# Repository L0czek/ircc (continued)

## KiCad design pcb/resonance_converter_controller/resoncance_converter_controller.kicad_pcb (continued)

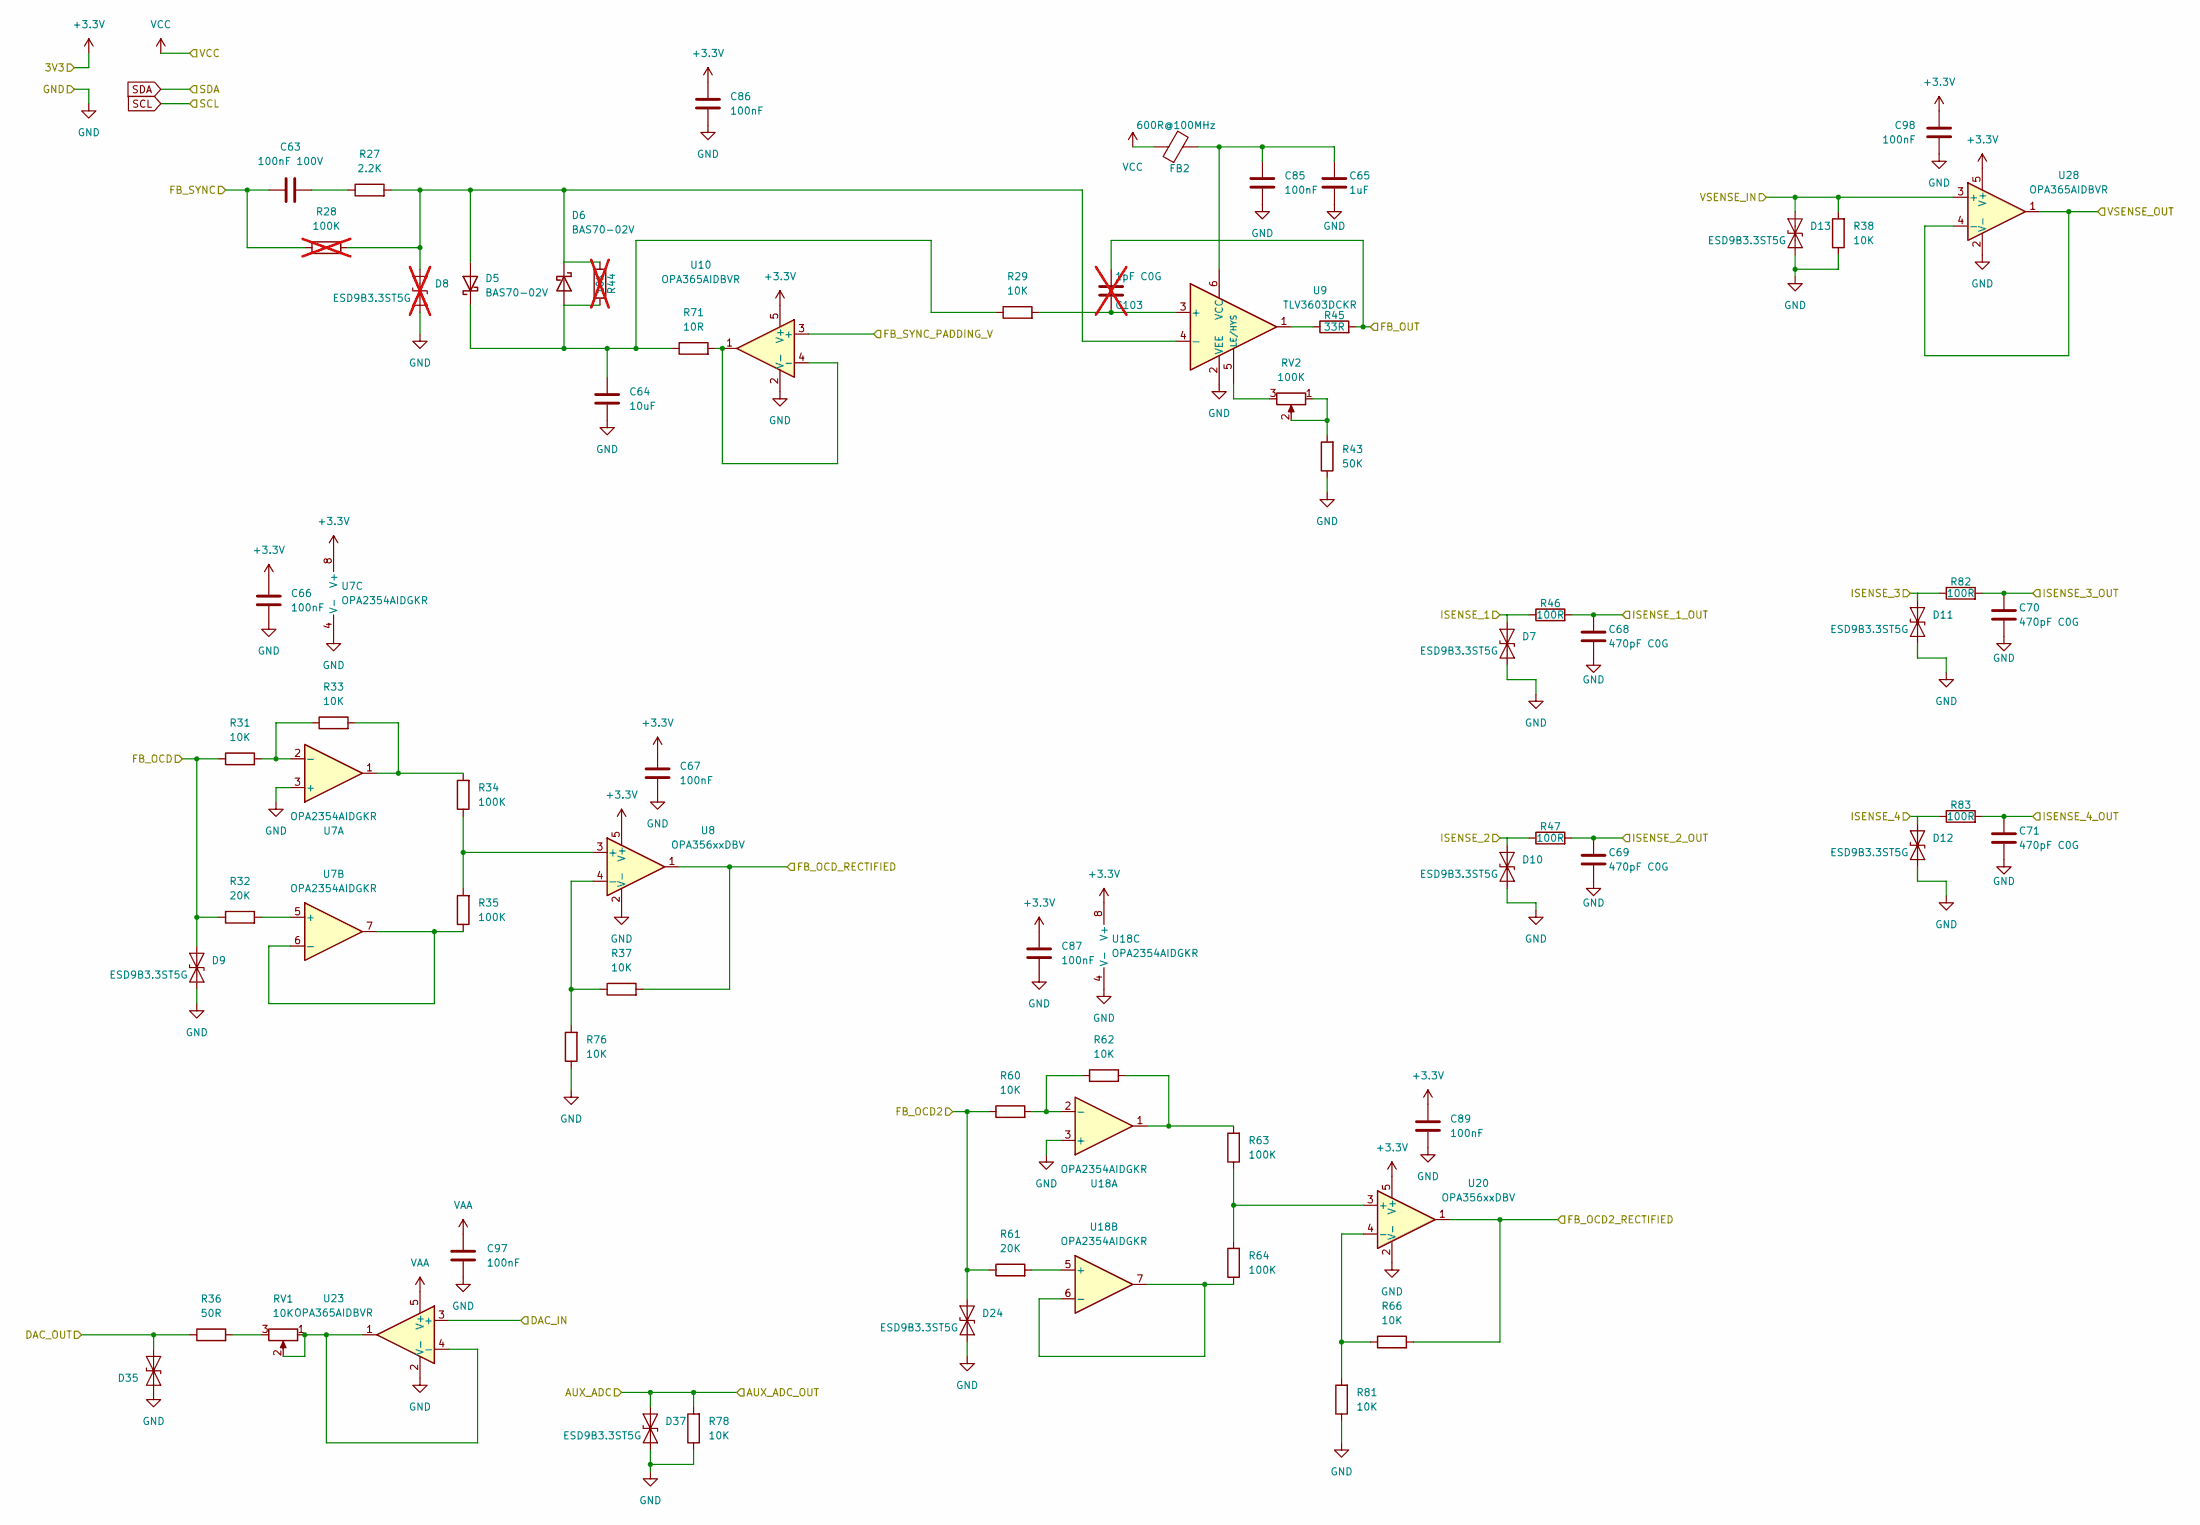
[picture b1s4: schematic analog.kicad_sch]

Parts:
C63: 100nF 100V; C_1206_3216Metric
C64: 10uF; C_1206_3216Metric
C65: 1uF; C_0402_1005Metric
C66, C67, C85, C86, C87, C89, C97, C98: 100nF; C_0402_1005Metric
C68, C69, C70, C71: 470pF C0G; C_0402_1005Metric
C103: 1pF C0G; C_0402_1005Metric; not fitted
D5, D6: BAS70-02V; D_SOD-523; MPN BAS7002VH6327XTSA1; LCSC C3312927
D7, D9, D10, D11, D12, D13, D24, D35, D37: ESD9B3.3ST5G; D_SOD-923
D8: ESD9B3.3ST5G; D_SOD-923; not fitted
FB2: 600R@100MHz; L_0603_1608Metric; MPN BLM18KG601SN1D; LCSC C85833
R27: 2.2K; R_2512_6332Metric
R28: 100K; R_1206_3216Metric; not fitted
R29, R31, R33, R37, R38, R60, R62, R66, R76, R78, R81: 10K; R_0402_1005Metric
R32, R61: 20K; R_0402_1005Metric
R34, R35, R63, R64: 100K; R_0402_1005Metric
R36: 50R; R_0402_1005Metric
R43: 50K; R_0402_1005Metric
R44: 10K; R_0402_1005Metric; not fitted
R45: 33R; R_0402_1005Metric
R46, R47, R82, R83: 100R; R_0402_1005Metric
R71: 10R; R_0402_1005Metric
RV1: 10K; Potentiometer_Bourns_3224J_Horizontal
RV2: 100K; Potentiometer_Bourns_3224J_Horizontal
U7, U18: OPA2354AIDGKR; VSSOP-8_3x3mm_P0.65mm; LCSC C95502
U8, U20: OPA356xxDBV; SOT-23-5
U9: TLV3603DCKR; SOT-363_SC-70-6; LCSC C5213955
U10, U23, U28: OPA365AIDBVR; SOT-23-5; LCSC C96626

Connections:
/Analog preprocess/DAC_IN: U23.3 (+); also elsewhere on the board
/Analog preprocess/FB_OCD2_RECTIFIED: R66.2, U20.1; also elsewhere on the board
/Analog preprocess/FB_OCD_RECTIFIED: R37.2, U8.1; also elsewhere on the board
/Analog preprocess/FB_OUT: C103.1, R45.2; also elsewhere on the board
/Analog preprocess/FB_SYNC_PADDING_V: U10.3 (+); also elsewhere on the board
/Analog preprocess/ISENSE_1_OUT: C68.1, R46.2; also elsewhere on the board
/Analog preprocess/ISENSE_2_OUT: C69.1, R47.2; also elsewhere on the board
/Analog preprocess/ISENSE_3_OUT: C70.1, R82.2; also elsewhere on the board
/Analog preprocess/ISENSE_4_OUT: C71.1, R83.2; also elsewhere on the board
/Analog preprocess/VSENSE_OUT: U28.1, U28.4 (-); also elsewhere on the board
AUX_ADC: D37.2 (A2), R78.2; also elsewhere on the board
DAC_OUT: D35.1 (A1), R36.1; also elsewhere on the board
FB_IN: C63.1, R28.1; also elsewhere on the board
GND: C64.1, C65.2, C66.1, C67.1, C68.2, C69.2, C70.2, C71.2, C85.1, C86.1, C87.1, C89.1, C97.2, C98.2, D7.1 (A1), D8.1 (A1), D9.1 (A1), D10.1 (A1), D11.1 (A1), D12.1 (A1), D13.1 (A1), D24.1 (A1), D35.2 (A2), D37.1 (A1), R38.1, R43.1, R76.1, R78.1, R81.1, U7.3 (+), U7.4 (V-), U8.2 (V-), U9.2 (VEE), U10.2 (V-), U18.3 (+), U18.4 (V-), U20.2 (V-), U23.2 (V-), U28.2 (V-); also elsewhere on the board
ISENSE_1: D7.2 (A2), R46.1; also elsewhere on the board
ISENSE_2: D10.2 (A2), R47.1; also elsewhere on the board
ISENSE_3: D11.2 (A2), R82.1; also elsewhere on the board
ISENSE_4: D12.2 (A2), R83.1; also elsewhere on the board
unnamed: C63.2, R27.1
unnamed: D5.2 (A), D6.1 (K), D8.2 (A2), R27.2, R28.2, R44.1, U9.4 (-)
unnamed: C64.2, D5.1 (K), D6.2 (A), R29.1, R44.2, R71.1
unnamed: R33.2, R34.2, U7.1
unnamed: R36.2, RV1.3
unnamed: R43.2, RV2.1, RV2.2
unnamed: R45.1, U9.1
unnamed: R62.2, R63.2, U18.1
unnamed: R31.2, R33.1, U7.2 (-)
unnamed: R32.2, U7.5 (+)
unnamed: R35.1, U7.6 (-), U7.7
unnamed: R34.1, R35.2, U8.3 (+)
unnamed: R37.1, R76.2, U8.4 (-)
unnamed: C103.2, R29.2, U9.3 (+)
unnamed: RV2.3, U9.5 (LE/HYS)
unnamed: C65.1, C85.2, FB2.2, U9.6 (VCC)
unnamed: R71.2, U10.1, U10.4 (-)
unnamed: R60.2, R62.1, U18.2 (-)
unnamed: R61.2, U18.5 (+)
unnamed: R64.1, U18.6 (-), U18.7
unnamed: R63.1, R64.2, U20.3 (+)
unnamed: R66.1, R81.2, U20.4 (-)
unnamed: RV1.1, RV1.2, U23.1, U23.4 (-)
OCD2_IN: D24.2 (A2), R60.1, R61.1; also elsewhere on the board
OCD_IN: D9.2 (A2), R31.1, R32.1; also elsewhere on the board
VAA: C66.2, C67.2, C86.2, C87.2, C89.2, C97.1, C98.1, U7.8 (V+), U8.5 (V+), U10.5 (V+), U18.8 (V+), U20.5 (V+), U23.5 (V+), U28.5 (V+); also elsewhere on the board
VCC: FB2.1; also elsewhere on the board
VSENSE_IN: D13.2 (A2), R38.2, U28.3 (+); also elsewhere on the board

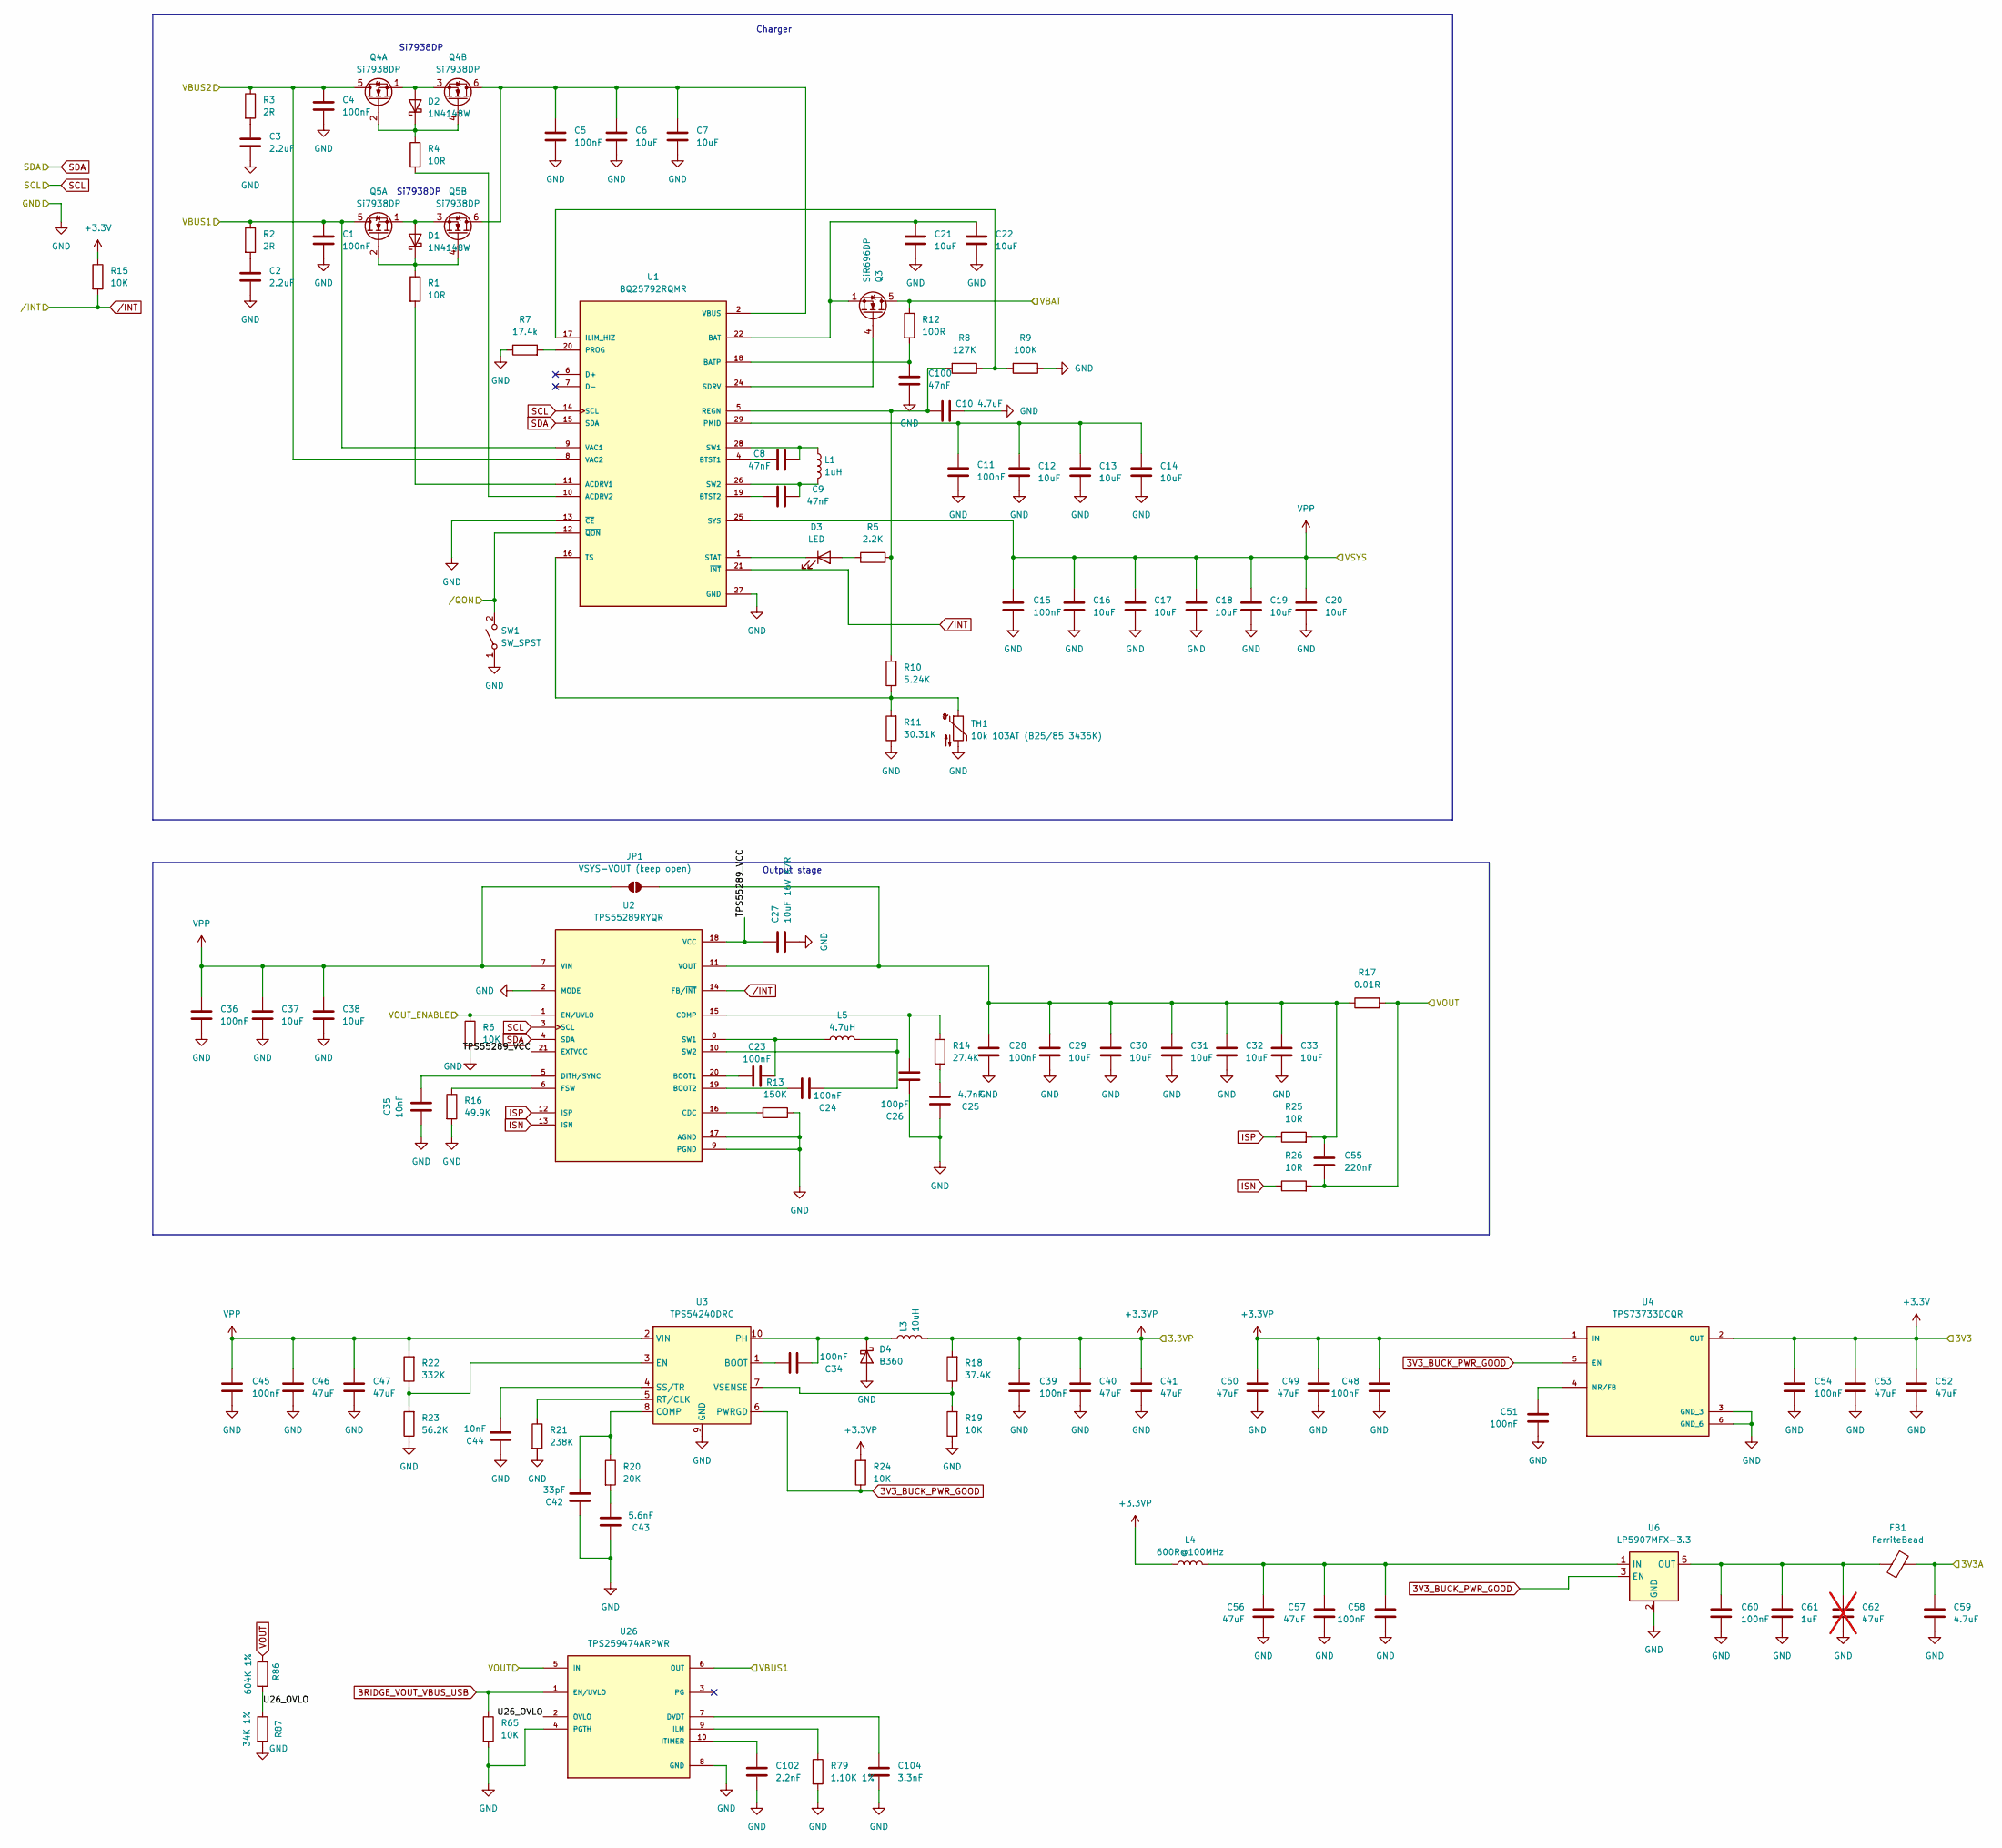
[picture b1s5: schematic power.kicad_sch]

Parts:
C1, C4, C5, C11, C15, C23, C24, C28, C34, C36, C39, C45, C48, C51, C54, C58, C60: 100nF; C_0402_1005Metric
C2, C3: 2.2uF; C_1206_3216Metric
C6, C7, C12, C13, C14, C16, C17, C18, C19, C20, C21, C22, C29, C30, C31, C32, C33, C37, C38: 10uF; C_1206_3216Metric
C8, C9, C100: 47nF; C_0402_1005Metric
C10: 4.7uF; C_1206_3216Metric
C25: 4.7nF; C_0402_1005Metric
C26: 100pF; C_0402_1005Metric
C27: 10uF 16V X7R; C_0805_2012Metric
C35, C44: 10nF; C_0402_1005Metric
C40, C41, C46, C47, C49, C50, C52, C53, C56, C57: 47uF; C_1206_3216Metric
C42: 33pF; C_0402_1005Metric
C43: 5.6nF; C_0402_1005Metric
C55: 220nF; C_0402_1005Metric
C59: 4.7uF; C_0805_2012Metric
C61: 1uF; C_0603_1608Metric
C62: 47uF; C_1206_3216Metric; not fitted
C102: 2.2nF; C_0402_1005Metric
C104: 3.3nF; C_0402_1005Metric
D1, D2: 1N4148W; D_SOD-123
D3: LED; LED_0805_2012Metric
D4: B360; D_SMB
FB1: FerriteBead; L_0805_2012Metric
JP1: VSYS-VOUT (keep open); SolderJumper-2_P1.3mm_Open_RoundedPad1.0x1.5mm
L1: 1uH; L_10.4x10.4_H4.8
L3: 10uH; C_2220_5750Metric
L4: 600R@100MHz; L_0805_2012Metric; MPN MPZ2012S601AT000; LCSC C21519
L5: 4.7uH; MPEV1D1040L4R7; MPN MPEV1D1040L4R7
Q3: SiR696DP; PowerPAK_SO-8_Single
Q4, Q5: Si7938DP; PowerPAK_SO-8_Dual
R1, R4, R25, R26: 10R; R_0402_1005Metric
R2, R3: 2R; R_1206_3216Metric
R5: 2.2K; R_0402_1005Metric
R6, R15, R19, R24, R65: 10K; R_0402_1005Metric
R7: 17.4k; R_0402_1005Metric
R8: 127K; R_0402_1005Metric
R9: 100K; R_0402_1005Metric
R10: 5.24K; R_0402_1005Metric
R11: 30.31K; R_0402_1005Metric
R12: 100R; R_0402_1005Metric
R13: 150K; R_0402_1005Metric
R14: 27.4K; R_0402_1005Metric
R16: 49.9K; R_0402_1005Metric
R17: 0.01R; R_1206_3216Metric
R18: 37.4K; R_0402_1005Metric
R20: 20K; R_0402_1005Metric
R21: 238K; R_0402_1005Metric
R22: 332K; R_0402_1005Metric
R23: 56.2K; R_0402_1005Metric
R79: 1.10K 1%; R_0402_1005Metric
R86: 604K 1%; R_0402_1005Metric
R87: 34K 1%; R_0402_1005Metric
SW1: SW_SPST; SW_SPST_EVQPE1
TH1: 10k 103AT (B25/85 3435K); R_0603_1608Metric; MPN NCP18XH103F03RB; LCSC C13564
U1: BQ25792RQMR; QFN40P400X400X100-29N; PARTREV 11/2019
U2: TPS55289RYQR; VREG_TPS55289RYQR; PARTREV August 2022
U3: TPS54240DRC; Texas_DRC0010J_ThermalVias
U4: TPS73733DCQR; IC_TPS73733DCQR; PARTREV R
U6: LP5907MFX-3.3; SOT-23-5
U26: TPS259474ARPWR; IC_TPS259474ARPWR; PARTREV A

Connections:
3V3_BUCK_PWR_GOOD: R24.1, U3.6 (PWRGD), U4.5 (EN), U6.3 (EN)
+3.3VP: C39.1, C40.1, C41.1, C48.1, C49.1, C50.1, L3.2, L4.1, R18.2, R24.2, U4.1 (IN); also elsewhere on the board
+BATT: Q3.5 (D), R12.1; also elsewhere on the board
/Controller/VOUT_ENABLE: R6.1, U2.1 (EN/UVLO); also elsewhere on the board
/Power supply/TPS55289_VCC: C27.1, U2.18 (VCC), U2.21 (EXTVCC)
/Power supply/U26_OVLO: R86.2, R87.1, U26.2 (OVLO)
BAT: C21.1, C22.1, Q3.1 (S), Q3.2 (S), Q3.3 (S), U1.22 (BAT), U1.23 (BAT)
BRIDGE_VOUT_VBUS_USB: R65.1, U26.1 (EN/UVLO); also elsewhere on the board
GND: C1.2, C2.2, C3.2, C4.2, C5.2, C6.2, C7.2, C10.2, C11.2, C12.2, C13.2, C14.2, C15.2, C16.2, C17.2, C18.2, C19.2, C20.2, C21.2, C22.2, C25.1, C26.1, C27.2, C28.2, C29.2, C30.2, C31.2, C32.2, C33.2, C35.1, C36.2, C37.2, C38.2, C39.2, C40.2, C41.2, C42.1, C43.1, C44.1, C45.2, C46.2, C47.2, C48.2, C49.2, C50.2, C51.2, C52.2, C53.2, C54.2, C56.2, C57.2, C58.2, C59.2, C60.2, C61.2, C62.2, C100.2, C102.2, C104.2, D4.2 (A), R6.2, R7.1, R9.1, R11.1, R13.1, R16.2, R19.1, R21.2, R23.1, R65.2, R79.2, R87.2, SW1.1 (A), TH1.2, U1.13 (~CE), U1.27 (GND), U2.2 (MODE), U2.9 (PGND), U2.17 (AGND), U3.9 (GND), U3.11 (GND), U4.3 (GND_3), U4.6 (GND_6), U6.2 (GND), U26.4 (PGTH), U26.8 (GND); also elsewhere on the board
INT_I2C_SCL: U1.14 (SCL), U2.3 (SCL); also elsewhere on the board
INT_I2C_SDA: U1.15 (SDA), U2.4 (SDA); also elsewhere on the board
ISN: R26.1, U2.13 (ISN)
ISP: R25.1, U2.12 (ISP)
unnamed: C2.1, R2.2
unnamed: C3.1, R3.2
unnamed: C25.2, R14.2
unnamed: C43.2, R20.2
unnamed: D1.2 (A), Q5.1 (S1), Q5.3 (S2)
unnamed: D1.1 (K), Q5.2 (G1), Q5.4 (G2), R1.1
unnamed: D2.2 (A), Q4.1 (S1), Q4.3 (S2)
unnamed: D2.1 (K), Q4.2 (G1), Q4.4 (G2), R4.1
unnamed: D3.2 (A), R5.1
unnamed: D3.1 (K), U1.1 (STAT)
unnamed: C34.1, D4.1 (K), L3.1, U3.10 (PH)
unnamed: C28.1, C29.1, C30.1, C31.1, C32.1, C33.1, C55.1, JP1.2 (B), R17.1, R25.2, U2.11 (VOUT)
unnamed: Q3.4 (G), U1.24 (SDRV)
unnamed: R1.2, U1.11 (ACDRV1)
unnamed: R4.2, U1.10 (ACDRV2)
unnamed: C100.1, R12.2, U1.18 (BATP)
unnamed: C8.1, U1.4 (BTST1)
unnamed: C9.1, U1.19 (BTST2)
unnamed: R8.1, R9.2, U1.17 (ILIM_HIZ)
unnamed: C11.1, C12.1, C13.1, C14.1, U1.29 (PMID)
unnamed: R7.2, U1.20 (PROG)
unnamed: C10.1, R5.2, R8.2, R10.2, U1.5 (REGN)
unnamed: C8.2, L1.1, U1.28 (SW1)
unnamed: C9.2, L1.2, U1.26 (SW2)
unnamed: R10.1, R11.2, TH1.1, U1.16 (TS)
unnamed: C23.1, U2.20 (BOOT1)
unnamed: C24.2, U2.19 (BOOT2)
unnamed: R13.2, U2.16 (CDC)
unnamed: C26.2, R14.1, U2.15 (COMP)
unnamed: C35.2, U2.5 (DITH/SYNC)
unnamed: R16.1, U2.6 (FSW)
unnamed: C23.2, L5.1, U2.8 (SW1)
unnamed: C24.1, L5.2, U2.10 (SW2)
unnamed: C34.2, U3.1 (BOOT)
unnamed: C42.2, R20.1, U3.8 (COMP)
unnamed: R22.1, R23.2, U3.3 (EN)
unnamed: R21.1, U3.5 (RT/CLK)
unnamed: C44.2, U3.4 (SS/TR)
unnamed: R18.1, R19.2, U3.7 (VSENSE)
unnamed: C51.1, U4.4 (NR/FB)
unnamed: C56.1, C57.1, C58.1, L4.2, U6.1 (IN)
unnamed: C60.1, C61.1, C62.1, FB1.1, U6.5 (OUT)
unnamed: C104.1, U26.7 (DVDT)
unnamed: R79.1, U26.9 (ILM)
unnamed: C102.1, U26.10 (ITIMER)
VAA: C59.1, FB1.2; also elsewhere on the board
VBUS: C5.1, C6.1, C7.1, Q4.6 (D2), Q5.6 (D2), U1.2 (VBUS), U1.3 (VBUS)
VBUS_DOCK: C4.1, Q4.5 (D1), R3.1, U1.8 (VAC2); also elsewhere on the board
VBUS_USBC: C1.1, Q5.5 (D1), R2.1, U1.9 (VAC1), U26.6 (OUT); also elsewhere on the board
VCC: C52.1, C53.1, C54.1, R15.1, U4.2 (OUT); also elsewhere on the board
VOUT: C55.2, R17.2, R26.2, R86.1, U26.5 (IN); also elsewhere on the board
VSYS: C15.1, C16.1, C17.1, C18.1, C19.1, C20.1, C36.1, C37.1, C38.1, C45.1, C46.1, C47.1, JP1.1 (A), R22.2, U1.25 (SYS), U2.7 (VIN), U3.2 (VIN); also elsewhere on the board
/INT: R15.2, U1.21 (~INT), U2.14 (FB/~INT); also elsewhere on the board
/QON: SW1.2 (B), U1.12 (~QON); also elsewhere on the board

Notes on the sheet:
Output stage
Si7938DP
Charger

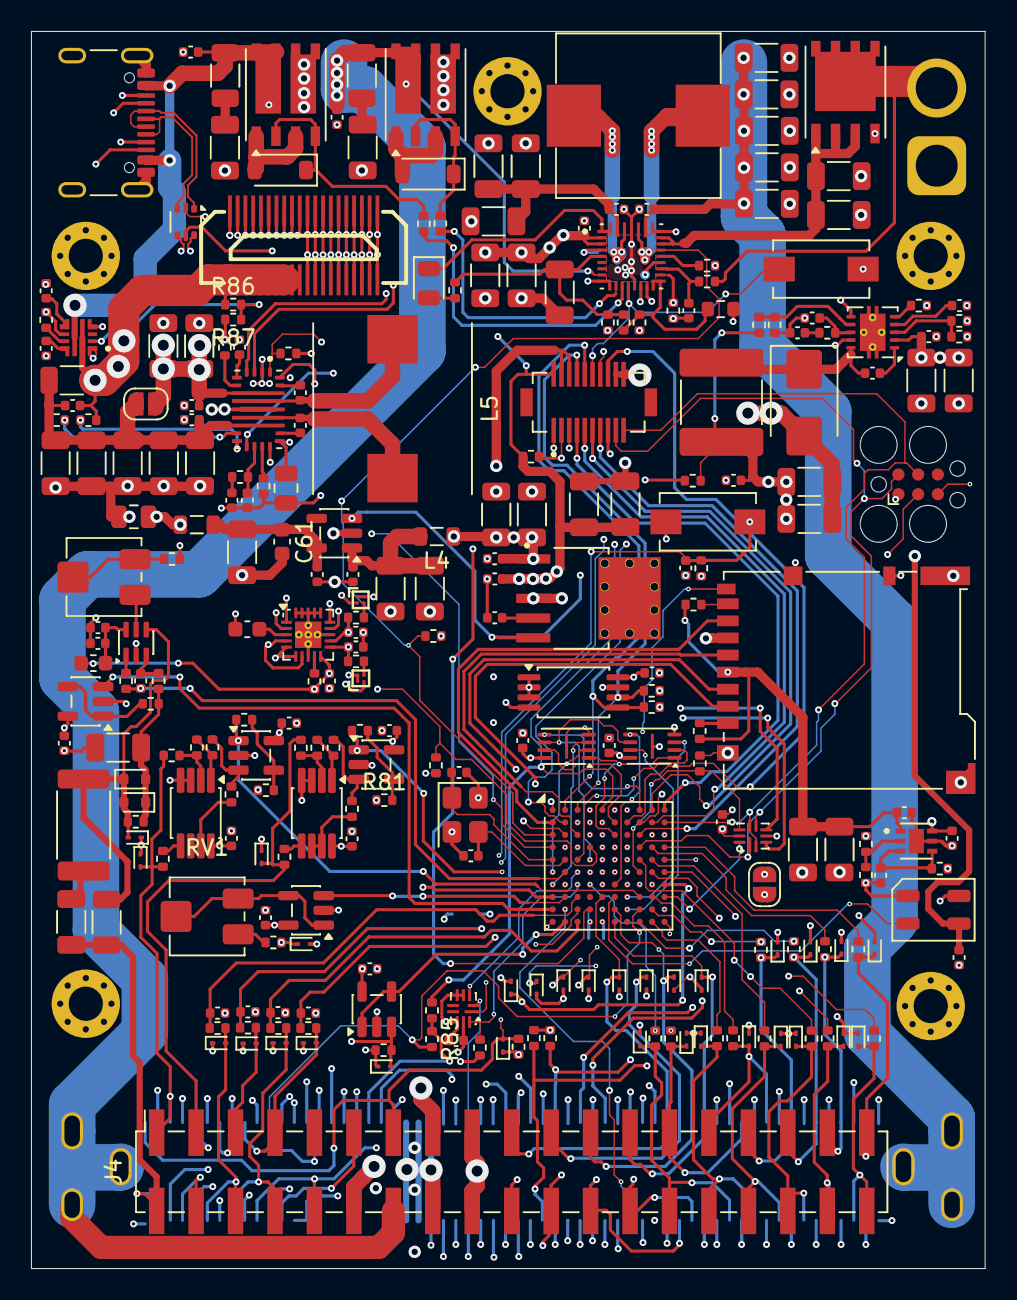
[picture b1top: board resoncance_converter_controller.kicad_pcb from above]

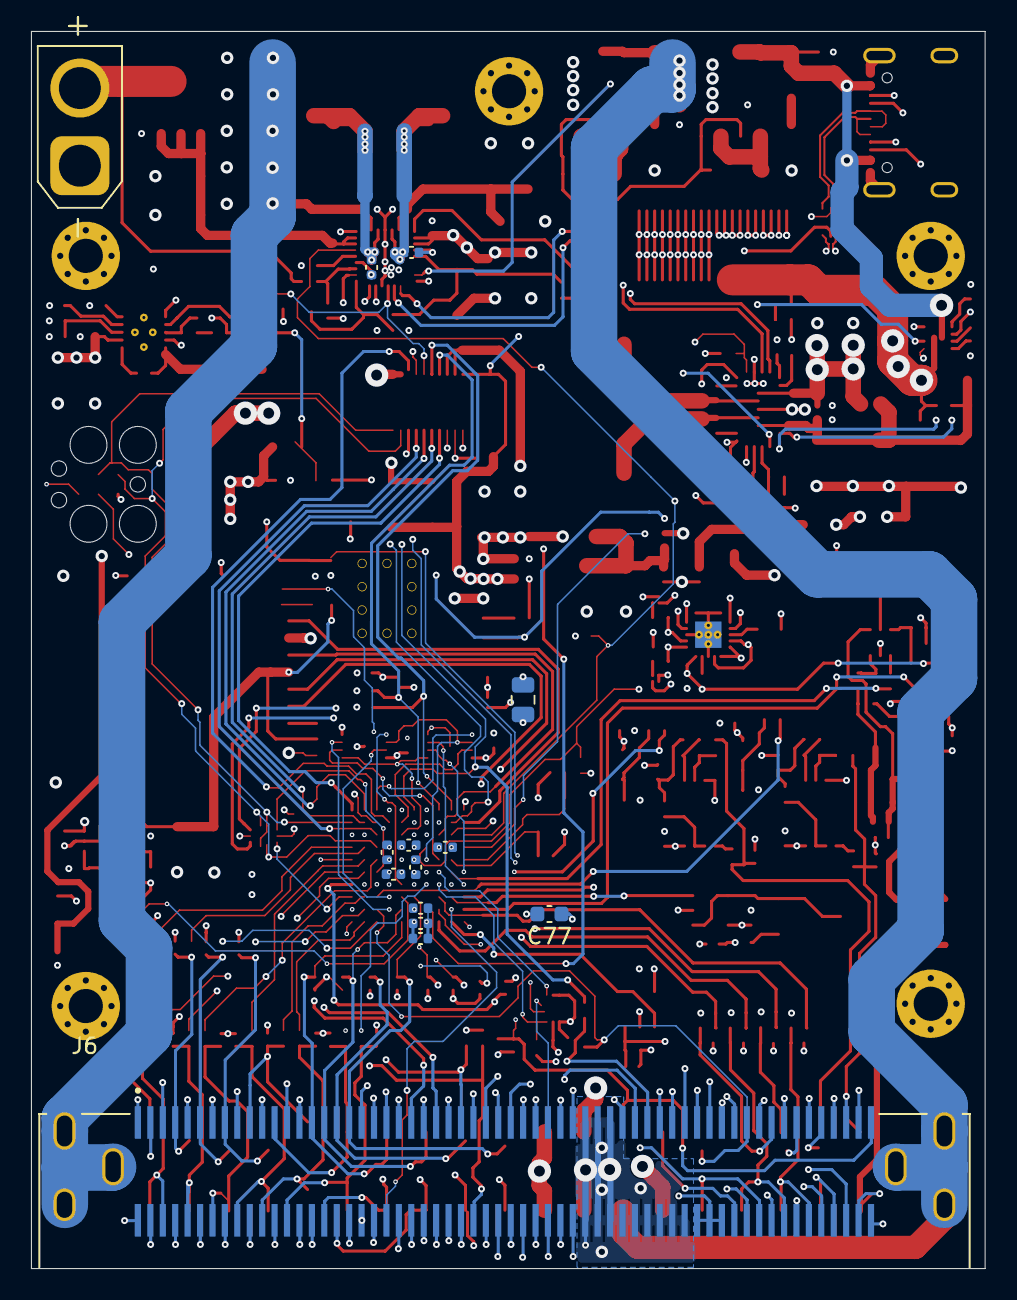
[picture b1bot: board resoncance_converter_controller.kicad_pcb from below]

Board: 6 copper layers, 61.4 x 79.7 mm, 289 parts (14 on the bottom side), 210 nets.

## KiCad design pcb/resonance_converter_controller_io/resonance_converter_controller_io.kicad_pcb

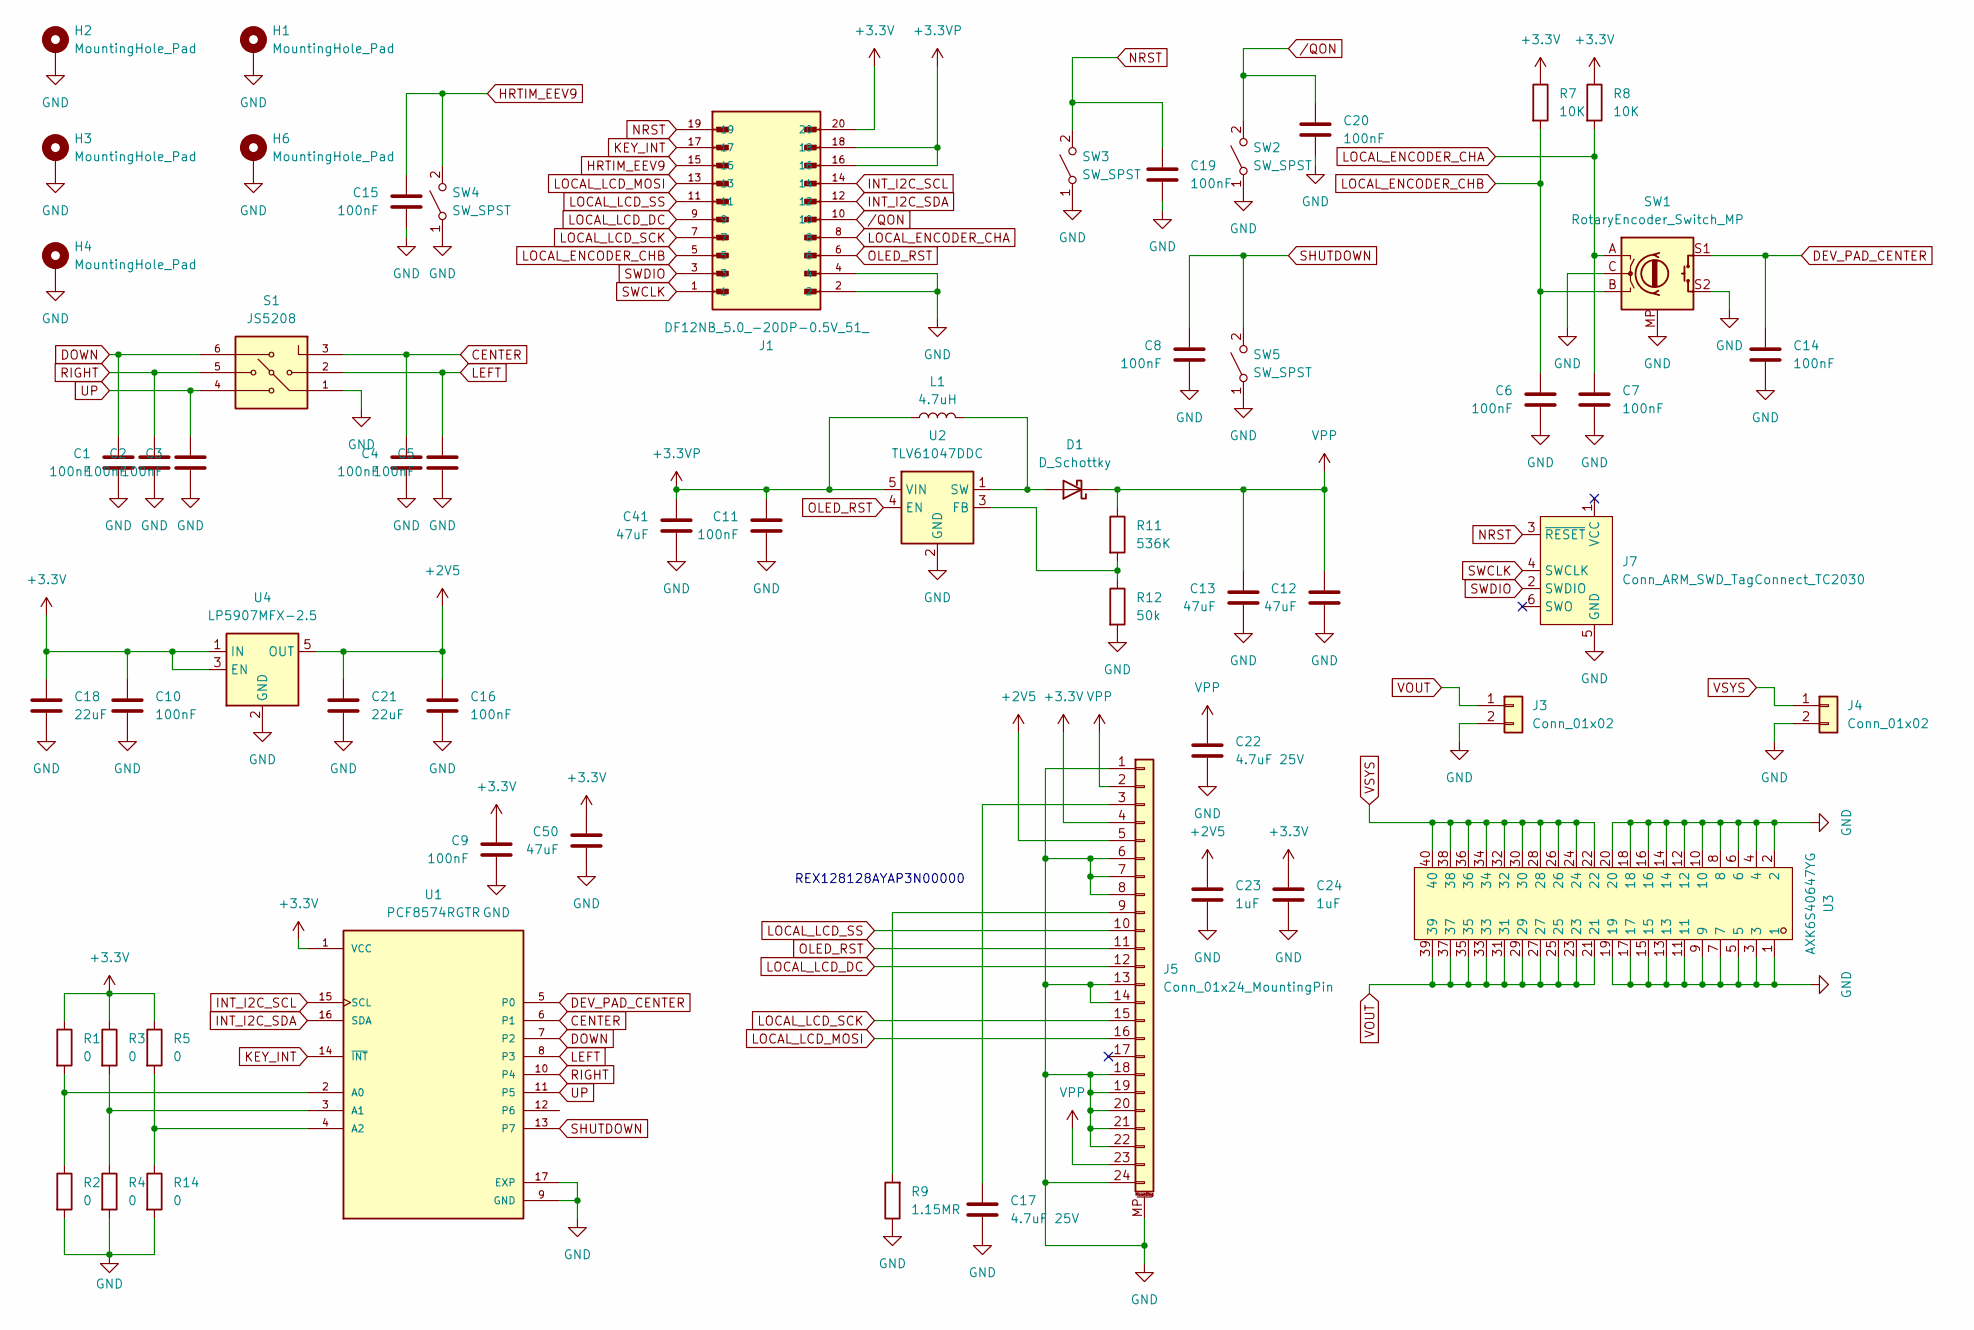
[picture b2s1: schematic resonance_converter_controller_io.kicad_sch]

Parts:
C1, C2, C3, C4, C5, C6, C7, C8, C9, C10, C11, C14, C15, C16, C19, C20: 100nF; C_0402_1005Metric
C12, C13, C41, C50: 47uF; C_1206_3216Metric
C17, C22: 4.7uF 25V; C_0805_2012Metric
C18, C21: 22uF; C_0805_2012Metric
C23, C24: 1uF; C_0402_1005Metric
D1: D_Schottky; D_SMA
H1, H2, H3, H4, H6: MountingHole_Pad; MountingHole_2.2mm_M2_Pad_Via
J1: DF12NB_5.0_-20DP-0.5V_51_; HRS_DF12NB_5.0_-20DP-0.5V_51_
J3, J4: Conn_01x02; PhoenixContact_MCV_1,5_2-G-3.5_1x02_P3.50mm_Vertical
J5: Conn_01x24_MountingPin; Hirose_FH12-24S-0.5SH_1x24-1MP_P0.50mm_Horizontal
J7: Conn_ARM_SWD_TagConnect_TC2030; Tag-Connect_TC2030-IDC-FP_2x03_P1.27mm_Vertical
L1: 4.7uH; L_1210_3225Metric
R1, R2, R3, R4, R5, R14: 0; R_0402_1005Metric
R7, R8: 10K; R_0402_1005Metric
R9: 1.15MR; R_0402_1005Metric
R11: 536K; R_0402_1005Metric
R12: 50k; R_0402_1005Metric
S1: JS5208; SW_JS5208; PARTREV D; DigiKey_Part_Number EG4561-ND
SW1: RotaryEncoder_Switch_MP; RotaryEncoder_Alps_EC11E-Switch_Vertical_H20mm_MountingHoles
SW2, SW3, SW4, SW5: SW_SPST; SW_SPST_EVQPE1
U1: PCF8574RGTR; QFN50P300X300X100-17N; PARTREV J; DigiKey_Part_Number 296-21238-1-ND
U2: TLV61047DDC; SOT-23-5
U3: AXK6S40647YG; CONN-SMD_40P_AXK6S40547YG; LCSC Part C3651273
U4: LP5907MFX-2.5; SOT-23-5

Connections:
+2V5: C16.1, C21.2, C23.1, J5.5, U4.5 (OUT)
+3.3V: C9.1, C10.1, C18.2, C24.1, C50.1, J1.20, J5.4, R1.1, R3.1, R5.1, R7.1, R8.1, U1.1 (VCC), U4.1 (IN), U4.3 (EN)
+3.3VP: C11.1, C41.1, J1.16, J1.18, L1.1, U2.5 (VIN)
CENTER: C4.1, S1.3, U1.6 (P1)
DEV_PAD_CENTER: C14.1, SW1.S1, U1.5 (P0)
DOWN: C1.1, S1.6, U1.7 (P2)
GND: C1.2, C2.2, C3.2, C4.2, C5.2, C6.2, C7.2, C8.2, C9.2, C10.2, C11.2, C12.2, C13.2, C14.2, C15.2, C16.2, C17.1, C18.1, C19.2, C20.2, C21.1, C22.1, C23.2, C24.2, C41.2, C50.2, H1.1 (1_1), H2.1 (1_1), H3.1 (1_1), H4.1 (1_1), H6.1 (1_1), J1.2, J1.4, J3.2, J4.2, J5.1, J5.6, J5.7, J5.8, J5.13, J5.14, J5.18, J5.19, J5.20, J5.21, J5.22, J5.24, J5.MP (MountPin), J7.5 (GND), R2.2, R4.2, R9.1, R12.2, R14.2, S1.1, SW1.C, SW1.MP, SW1.S2, SW2.1 (A), SW3.1 (A), SW4.1 (A), SW5.1 (A), U1.9 (GND), U1.17 (EXP), U2.2 (GND), U3.1, U3.2, U3.3, U3.4, U3.5, U3.6, U3.7, U3.8, U3.9, U3.10, U3.11, U3.12, U3.13, U3.14, U3.15, U3.16, U3.17, U3.18, U3.19, U3.20, U4.2 (GND)
HRTIM_EEV9: C15.1, J1.15, SW4.2 (B)
INT_I2C_SCL: J1.14, U1.15 (SCL)
INT_I2C_SDA: J1.12, U1.16 (SDA)
KEY_INT: J1.17, U1.14 (~INT)
LEFT: C5.1, S1.2, U1.8 (P3)
LOCAL_ENCODER_CHA: C7.1, J1.8, R8.2, SW1.A
LOCAL_ENCODER_CHB: C6.1, J1.5, R7.2, SW1.B
LOCAL_LCD_DC: J1.9, J5.12
LOCAL_LCD_MOSI: J1.13, J5.16
LOCAL_LCD_SCK: J1.7, J5.15
LOCAL_LCD_SS: J1.11, J5.10
NRST: C19.1, J1.19, J7.3 (~RESET), SW3.2 (B)
unnamed: D1.2 (A), L1.2, U2.1 (SW)
unnamed: C17.2, J5.3
unnamed: J5.9, R9.2
unnamed: R1.2, R2.1, U1.2 (A0)
unnamed: R3.2, R4.1, U1.3 (A1)
unnamed: R5.2, R14.1, U1.4 (A2)
unnamed: R11.2, R12.1, U2.3 (FB)
OLED_RST: J1.6, J5.11, U2.4 (EN)
RIGHT: C2.1, S1.5, U1.10 (P4)
SHUTDOWN: C8.1, SW5.2 (B), U1.13 (P7)
SWCLK: J1.1, J7.4 (SWCLK)
SWDIO: J1.3, J7.2 (SWDIO)
UP: C3.1, S1.4, U1.11 (P5)
VOUT: J3.1, U3.21, U3.23, U3.25, U3.27, U3.29, U3.31, U3.33, U3.35, U3.37, U3.39
VPP: C12.1, C13.1, C22.2, D1.1 (K), J5.2, J5.23, R11.1
VSYS: J4.1, U3.22, U3.24, U3.26, U3.28, U3.30, U3.32, U3.34, U3.36, U3.38, U3.40
/QON: C20.1, J1.10, SW2.2 (B)

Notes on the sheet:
REX128128AYAP3N00000
